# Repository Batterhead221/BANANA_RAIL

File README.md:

# banana_rail (pwr_supply_board)

dev board - will not fab

# BANANA_RAIL (PWR_SUPPLY_BOARD)

Compact fixed-output bench power supply PCB designed for prototyping, and breadboard power. 
Rev A — Functional prototype
Designed for 1A output applications (Arduino, ESP32, sensors, logic circuits)

designed & engineered by brandon shelly

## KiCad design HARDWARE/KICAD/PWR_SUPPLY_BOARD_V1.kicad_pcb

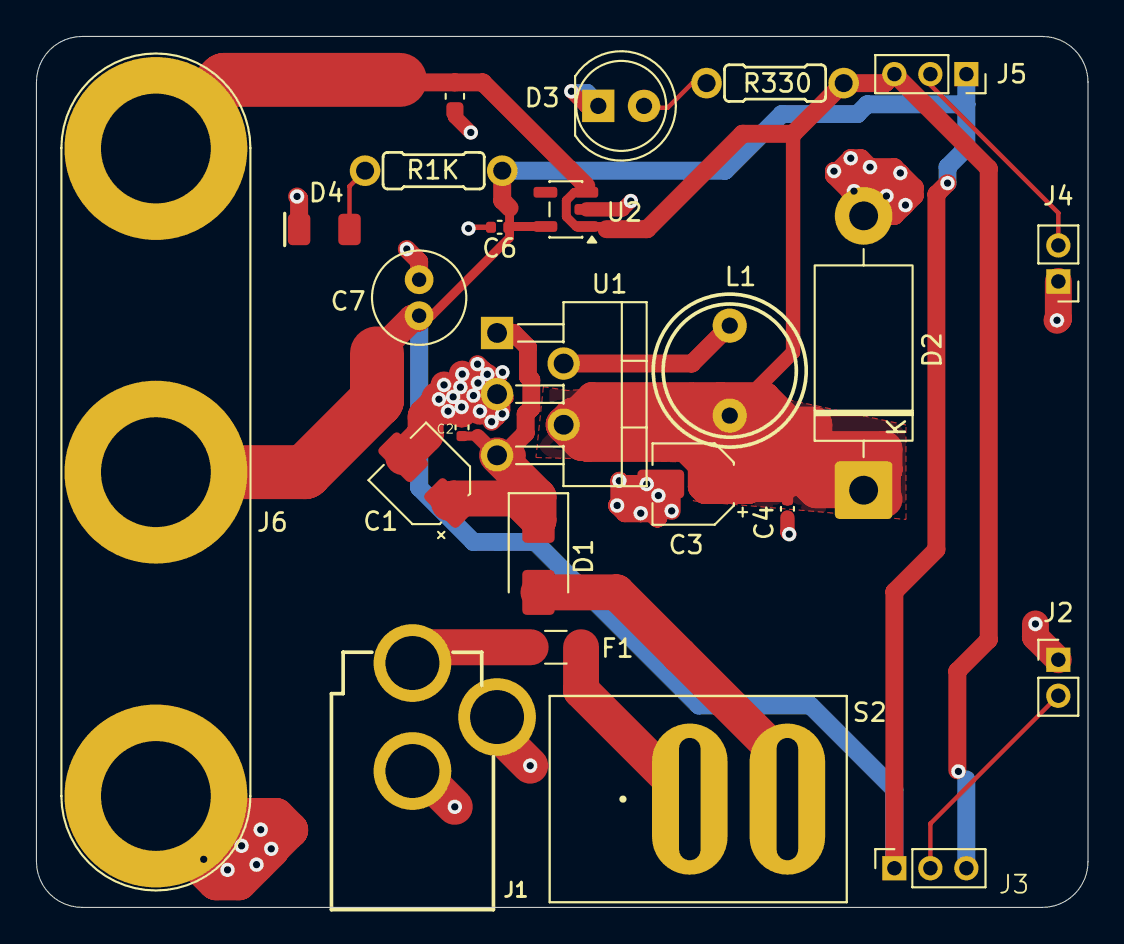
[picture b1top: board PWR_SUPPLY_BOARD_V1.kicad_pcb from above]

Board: 2 copper layers, 58.4 x 48.4 mm, 24 parts (0 on the bottom side), 12 nets.

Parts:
C1: 470UF_50V; CP_Elec_4x5.3
C2, C4, C6: 0.1UF; C_0402_1005Metric
C3: 220UF 25V; CP_Elec_4x5.3
C5: 1UF; C_0603_1608Metric
C7: 10UF; C_Radial_D5.0mm_H11.0mm_P2.00mm
D1: SS14; D_SMA
D2: 5A_40V; D_DO-201AD_P15.24mm_Horizontal
D3: LED; LED_D5.0mm_FlatTop
D4: Green; LED_1206_3216Metric_Green
F1: 1.5A; Fuse_1206_3216Metric
J1: Barrel_Jack_PTH
J2, J4: Conn_01x02_Pin; PinHeader_1x02_P2.00mm_Vertical
J3, J5: Conn_01x03_Pin; PinSocket_1x03_P2.00mm_Vertical
J6: BANANA_CONN; Banana_Jack_3Pin
L1: RLB0913-273K (68UH); RLB0913-273K
R1K: 1K; Resistor_14w
R330: 330; Resistor_14w
S2: RB141C1100; SW_RB141C1100
U1: LM2596-5.0; TO-220-5_P3.4x3.7mm_StaggerOdd_Lead3.8mm_Vertical
U2: AP2112K-3.3; SOT-23-5

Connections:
/+3.3V: C6.1, C7.1, J3.1, J5.1, J6.2 (YELLOW), R1K.1, U2.5 (VOUT)
/+5V: C3.1, C4.1, C5.1, D2.1 (K), J3.3, J5.3, J6.3 (RED), L1.2, R330.1, U1.4 (FB), U2.1 (VIN), U2.3 (EN)
/+12V: C1.1, C2.1, D1.1 (K), U1.1 (VIN), U1.5 (~ON/OFF)
/PWR_IN: F1.1, J1.1 (PWR)
GND: C1.2, C2.2, C3.2, C4.2, C5.2, C6.2, C7.2, D2.2 (A), D3.1 (K), D4.1 (K), J1.2 (GND), J1.3 (GNDBREAK), J2.1, J4.1, J6.1 (GND), U1.3 (GND), U2.2 (GND)
unnamed: D1.2 (A), S2.2
unnamed: D3.2 (A), R330.2
unnamed: D4.2 (A), R1K.2
unnamed: F1.2, S2.1
unnamed: J2.2, J3.2
unnamed: J4.2, J5.2
unnamed: L1.1, U1.2 (OUT)

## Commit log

2026-02-15 UPDATES
    CLEANED UP REPO
2026-03-03 UPDATE
    UPDATE
2026-03-21 PUSH
2026-04-18 file path restructure
2026-05-03 folder restructure
